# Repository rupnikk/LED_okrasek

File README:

Urban Rupnik
Zadlog 42
LED_okrasek

-------------------------------------------------------

PCB verzija 1.1 (december 2016)

********SPREMEMBE************
- dovolj velik procesor(ne vem koliko prostora bodo zasedle melodije, tudi zaradi I2C in USART)
- IR oddajnik in sprejemnik (za 36 kHz in 38 kHz)
- en input gumb
- 8 led 
- 1W ojačevalnik
- zvočnik
- porti povezani precej naključno (en prvih tudi programerskih projektov)

PCB verzija 1.2 (januar 2017)
- dovolj velik procesor(ne vem koliko prostora bodo zasedle melodije)
- IR oddajnik in sprejemnik (za 36 kHz in 38 kHz)
- en input gumb
- 8 led 
- 1W ojačevalnik
- zvočnik

********SPREMEMBE************
- BTN na pin 32 (tam je možnost INT, ne samo PCINT)
- IR_REC na pin 1 (tam je možnost INT, ne samo PCINT)
- IR_LED na pin 15 (PB3)(OC2A)(niso iste nastavitve kot pri timerju-0 za AUDIO))(ne na pin 11, zato ker se nastavitev timerja 1 ne bodo mogle prilagajat, zaradi branja daljinca)
-prilagoditev LED-ic

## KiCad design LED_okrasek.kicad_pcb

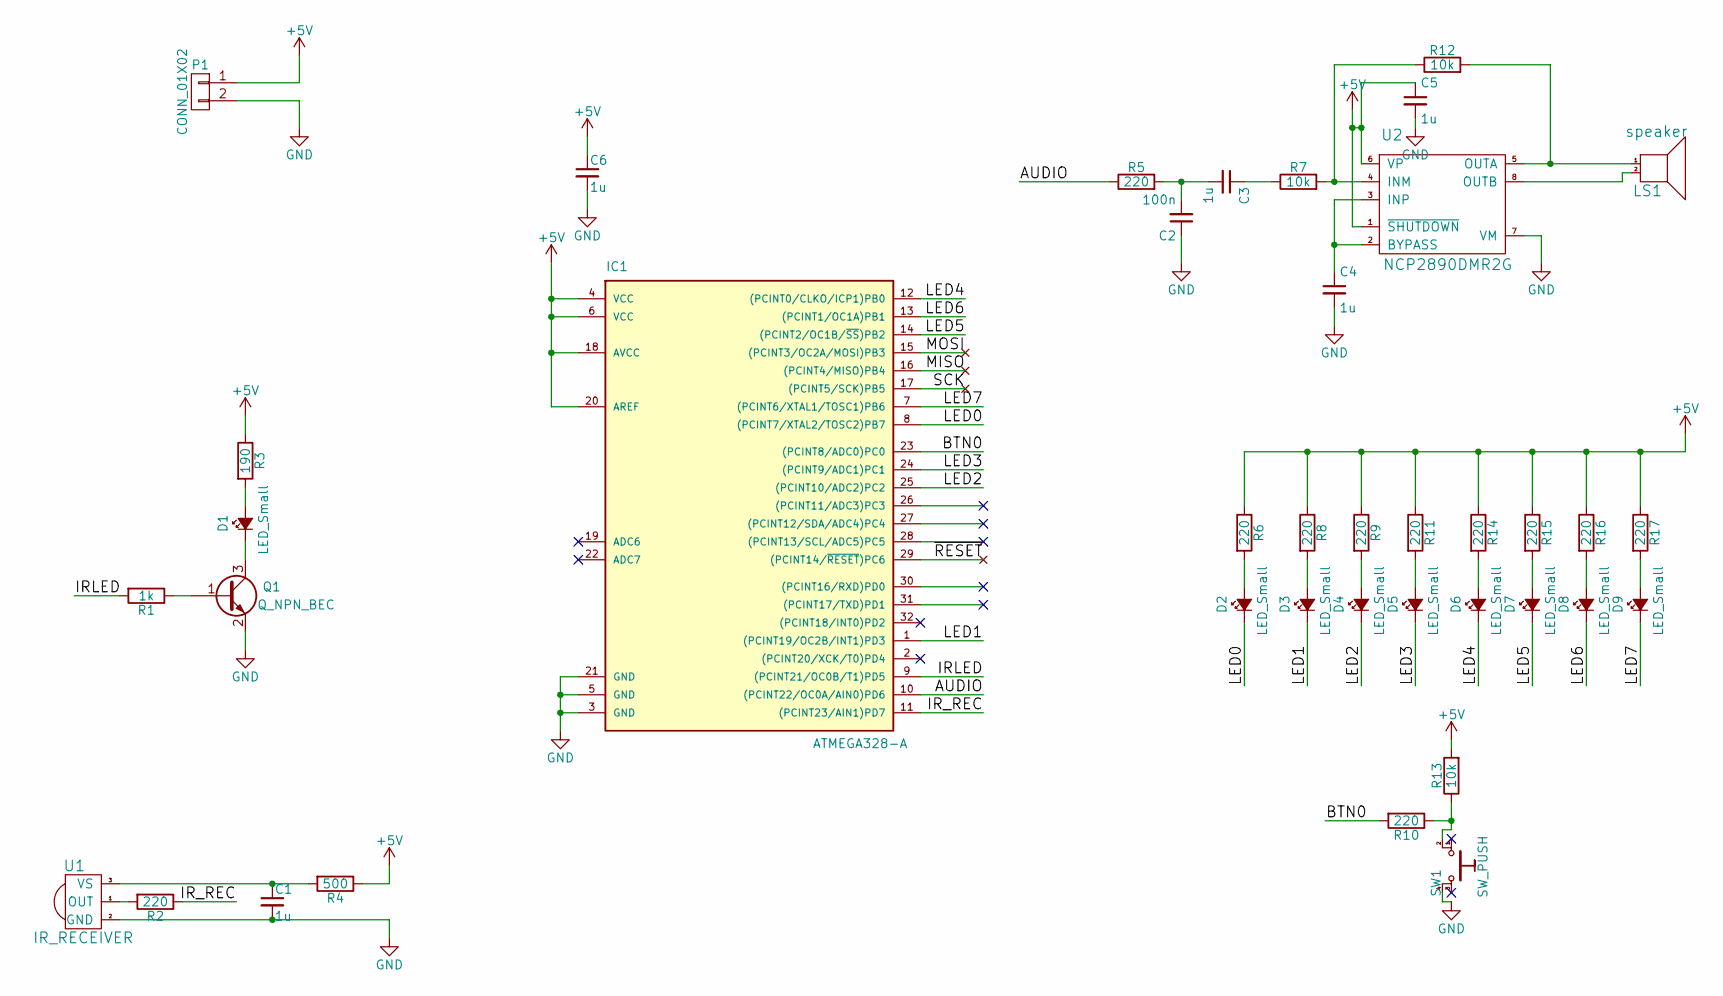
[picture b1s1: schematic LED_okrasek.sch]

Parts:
C1, C3, C4, C6: 1u; C_0603_HandSoldering
C2: 100n; C_0603_HandSoldering
C5: 1u; R_0603_HandSoldering
D1: LED_Small; R_0603_HandSoldering; Farnell number 2290428
D2, D3, D4, D5, D6, D7, D8, D9: LED_Small; LED_0_1inch
IC1: ATMEGA328-A; TQFP-32_7x7mm_Pitch0.8mm; Farnell number 2443176
LS1: speaker; Speaker; Farnelll number 2396077
P1: CONN_01X02; CONN_2x1x5.08
PAD1, PAD2, PAD3, PAD4: PAD
Q1: Q_NPN_BEC; SOT-23_Handsoldering; Farnell number 8737070
R1: 1k; R_0603_HandSoldering
R2, R5, R6, R8, R9, R10, R11, R14, R15, R16, R17: 220; R_0603_HandSoldering
R3: 190; R_0603_HandSoldering
R4: 500; R_0603_HandSoldering
R7, R12, R13: 10k; R_0603_HandSoldering
SW1: SW_PUSH; TACTILE_SWTICH_4PIN_SMD
U1: IR_RECEIVER; TSOP; Farnell number 2251356
U2: NCP2890DMR2G; Micro8_SMD; Farnell number 2464740

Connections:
+5V: C5.1, C6.1, IC1.4 (VCC), IC1.6 (VCC), IC1.18 (AVCC), IC1.20 (AREF), P1.1, R3.1, R4.1, R6.1, R8.1, R9.1, R11.1, R13.2, R14.1, R15.1, R16.1, R17.1, U2.1 (~SHUTDOWN), U2.6 (VP)
/AUDIO: IC1.10 ((PCINT22/OC0A/AIN0)PD6), R5.1
/BTN0: IC1.23 ((PCINT8/ADC0)PC0), R10.2
/IRLED: IC1.9 ((PCINT21/OC0B/T1)PD5), R1.2
/IR_REC: IC1.11 ((PCINT23/AIN1)PD7), R2.1
/LED0: D2.1 (K), IC1.8 ((PCINT7/XTAL2/TOSC2)PB7)
/LED1: D3.1 (K), IC1.1 ((PCINT19/OC2B/INT1)PD3)
/LED2: D4.1 (K), IC1.25 ((PCINT10/ADC2)PC2)
/LED3: D5.1 (K), IC1.24 ((PCINT9/ADC1)PC1)
/LED4: D6.1 (K), IC1.12 ((PCINT0/CLKO/ICP1)PB0)
/LED5: D7.1 (K), IC1.14 ((PCINT2/OC1B/~SS~)PB2)
/LED6: D8.1 (K), IC1.13 ((PCINT1/OC1A)PB1)
/LED7: D9.1 (K), IC1.7 ((PCINT6/XTAL1/TOSC1)PB6)
/MISO: IC1.16 ((PCINT4/MISO)PB4), PAD2.1
/MOSI: IC1.15 ((PCINT3/OC2A/MOSI)PB3), PAD1.1
/SCK: IC1.17 ((PCINT5/SCK)PB5), PAD3.1
/~RESET: IC1.29 ((PCINT14/~RESET~)PC6), PAD4.1
GND: C1.2, C2.1, C4.2, C5.2, C6.2, IC1.3 (GND), IC1.5 (GND), IC1.21 (GND), P1.2, Q1.2 (E), SW1.4, U1.2 (GND), U2.7 (VM)
unnamed: C1.1, R4.2, U1.3 (VS)
unnamed: C2.2, C3.2, R5.2
unnamed: C3.1, R7.1
unnamed: C4.1, U2.2 (BYPASS), U2.3 (INP)
unnamed: D1.1 (K), Q1.3 (C)
unnamed: D1.2 (A), R3.2
unnamed: D2.2 (A), R6.2
unnamed: D3.2 (A), R8.2
unnamed: D4.2 (A), R9.2
unnamed: D5.2 (A), R11.2
unnamed: D6.2 (A), R14.2
unnamed: D7.2 (A), R15.2
unnamed: D8.2 (A), R16.2
unnamed: D9.2 (A), R17.2
unnamed: LS1.1 (A), R12.2, U2.5 (OUTA)
unnamed: LS1.2 (B), U2.8 (OUTB)
unnamed: Q1.1 (B), R1.1
unnamed: R2.2, U1.1 (OUT)
unnamed: R10.1, R13.1, SW1.2
unnamed: R7.2, R12.1, U2.4 (INM)

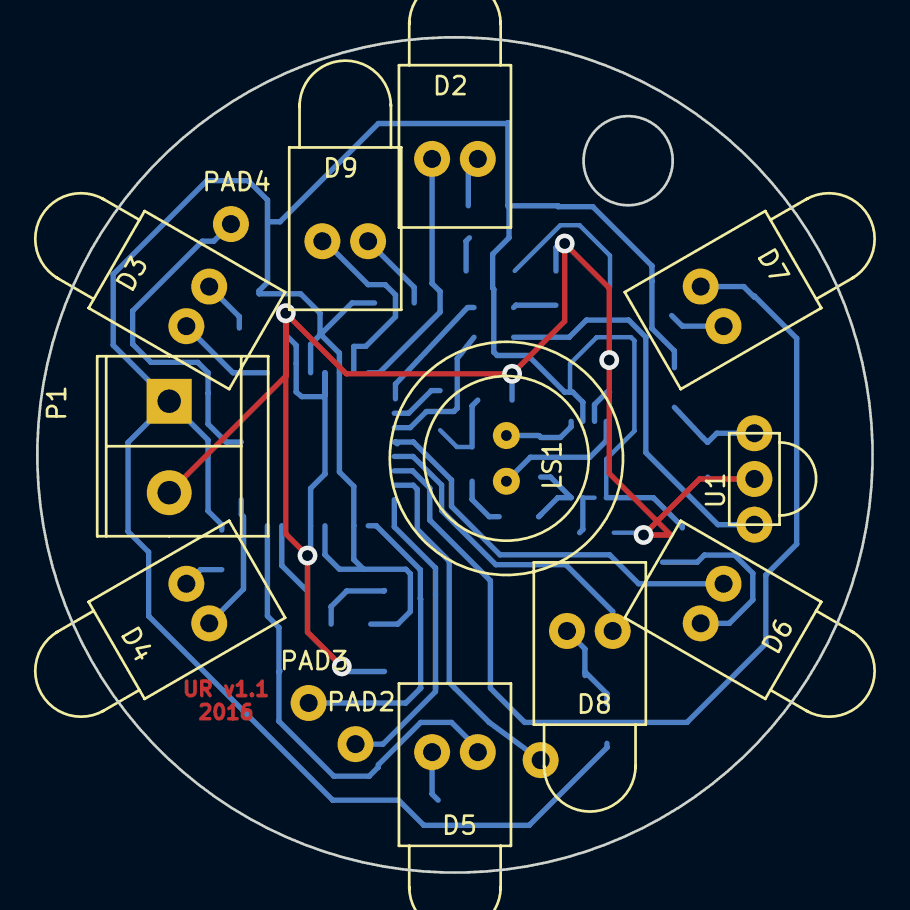
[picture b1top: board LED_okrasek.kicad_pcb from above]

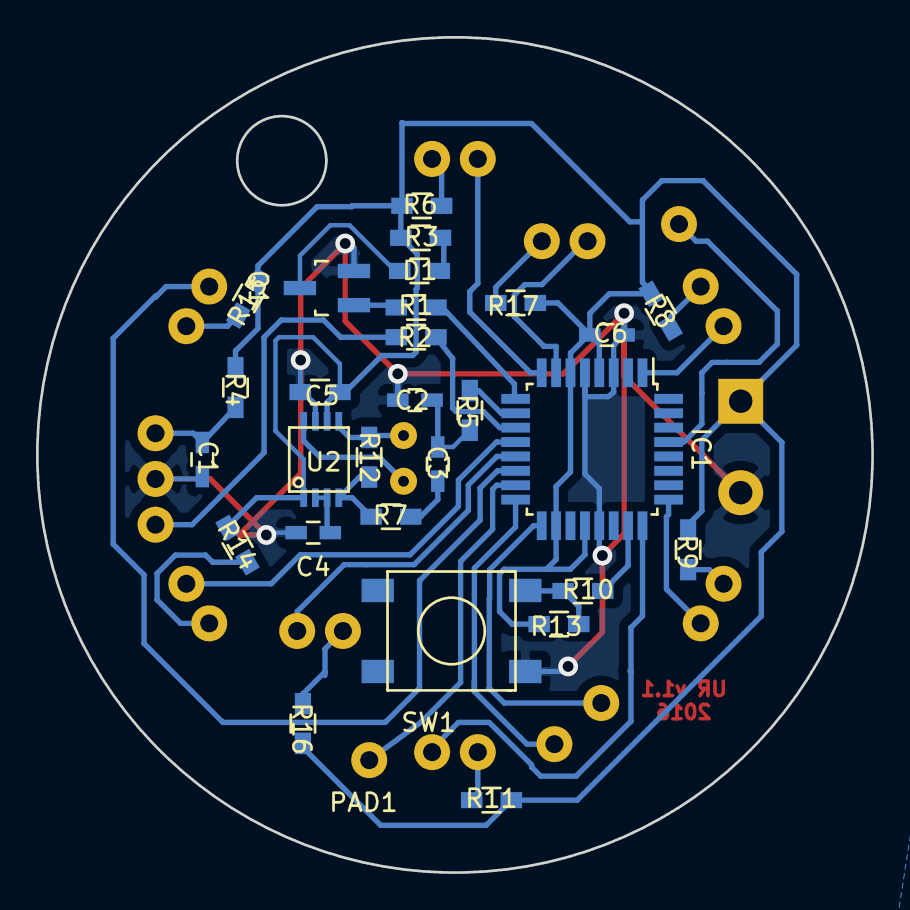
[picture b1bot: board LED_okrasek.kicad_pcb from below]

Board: 2 copper layers, 46.4 x 46.4 mm, 43 parts (29 on the bottom side), 38 nets.

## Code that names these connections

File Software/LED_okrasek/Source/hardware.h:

/*
 * hardware.h
 *
 *  Created on: 19. dec. 2016
 *      Author: Urban Rupnik
 *      City: Zadlog 42
 */
#include <avr/io.h>

#ifndef _HARDWARE_H_
#define _HARDWARE_H_



/*******************************
 *************LEDICE************
 *******************************/
#define LED0 PB7
#define LED1 PD3
#define LED2 PC2
#define LED3 PC1
#define LED4 PB0
#define LED5 PB2
#define LED6 PB1
#define LED7 PB6

#define LED0_PORT PORTB
#define LED1_PORT PORTD
#define LED2_PORT PORTC
#define LED3_PORT PORTC
#define LED4_PORT PORTB
#define LED5_PORT PORTB
#define LED6_PORT PORTB
#define LED7_PORT PORTB


#define LED0_DIR_PORT DDRB
#define LED1_DIR_PORT DDRD
#define LED2_DIR_PORT DDRC
#define LED3_DIR_PORT DDRC
#define LED4_DIR_PORT DDRB
#define LED5_DIR_PORT DDRB
#define LED6_DIR_PORT DDRB
#define LED7_DIR_PORT DDRB

#define LED5_PWM OC1B
#define LED5_PWM_CTR_REG TCCR1A

/*******************************
 ************ZVOČNIK************
 *******************************/
#define AUDIO PD6
#define AUDIO_PORT	PORTD
#define AUDIO_DIR_PORT	DDRD
#define AUDIO_PWM



/*******************************
 *************IR LED************
 *******************************/
#define IR_LED PD5
#define IR_LED_PORT	PORTD
#define IR_LED_DIR_PORT	DDRD



/*******************************
 ***********IR RECEIVER*********
 *******************************/

#define IR_REC PD7
#define IR_REC_PORT	PORTD
#define IR_REC_DIR_PORT	DDRD
#define IR_REC_VALUE_REG PIND
#define IR_REC_PCINT PCINT23

/*******************************
 *************BUTTON************
 *******************************/
#define BTN PC0
#define BTN_PORT PORTC
#define BTN_DIR_PORT DDRC
#define BTN_VALUE_REG PINC
#define BTN_PCINT PCINT8


#endif
